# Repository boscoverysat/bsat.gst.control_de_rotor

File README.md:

# Control de Rotor

## Resumen

Este repositorio contiene la adaptación de la electrónica de control empleada para el rotor de antena basado en el proyecto **[SatNOGS](https://satnogs.org/)**

## Autoría y Licencia

- Autor: **Dailos Rafael Díaz Lara** ( ddialar@gmail.com )
- Fecha: **11/09/2015**
- Versión: **1.0.0**
- Licencia: 

## Requisitos previos

- Tener instalado el entorno de desarrollo para Arduino.
- Tener instalado el software Eagle PCB 6.5.0+.

## Procedimiento

Este repositorio contiene la adaptación de la electrónica de control empleada para el rotor de antena basado en el proyecto **[SatNOGS](https://satnogs.org/)** ([Repositorio de origen](https://github.com/satnogs/satnogs-rotator-controller)).

Esta adaptación se ha realizado para utilizar una placa **Ardino Duemilanove** en lugar de la placa *Ardiono Pro Micro*
empleada originalmente.

Para poder llevar a cabo esta adaptación, además de reorganizar la electrónica en torno a los pines del Arduino a emplear,
ha sido necesario reconfigurar los pines dentro del código fuente que será cargado en el microcontrolador.

La organización de directorios de este repositorio es la siguiente:

### [arduino](arduino/)

Contiene el archivo de código fuente que debe cargarse en el microcontrolador.

Para que este script funcione, es necesario incorporar en nuestro entorno de desarrollo, una librería adicional
que no suele venir con la instalación estándar. Dicha librería es **AccelStepper.h** y puede ser localizada
en el siguiente [enlace](https://github.com/adafruit/AccelStepper).

Para concluir, hay que indicar que la única diferencia entre el script original y el empleado en este repositorio, reside en que se ha modificado la numeración de los pines empleados para el control de los motores paso a paso, así como para la detección de la posición HOME de los ejes de Elevación y Azimuth.

En el código fuente que contiene el directorio, se ha mantenido la definición original de pines (comentada para que no tenga efecto en el código), con el propósito que sirva de referencia en futuras investigaciones.

### [img](img/)

Contiene una imagen del conexionado de la placa PCB.

### [pcb](pcb/)

Contiene el proyecto de placa de circuito impreso, realizado con el software **Eagle 6.5.0**.

### [pdf](pdf/)

Contiene el esquema electrónico y el diagrama PCB listos para ser impresos.

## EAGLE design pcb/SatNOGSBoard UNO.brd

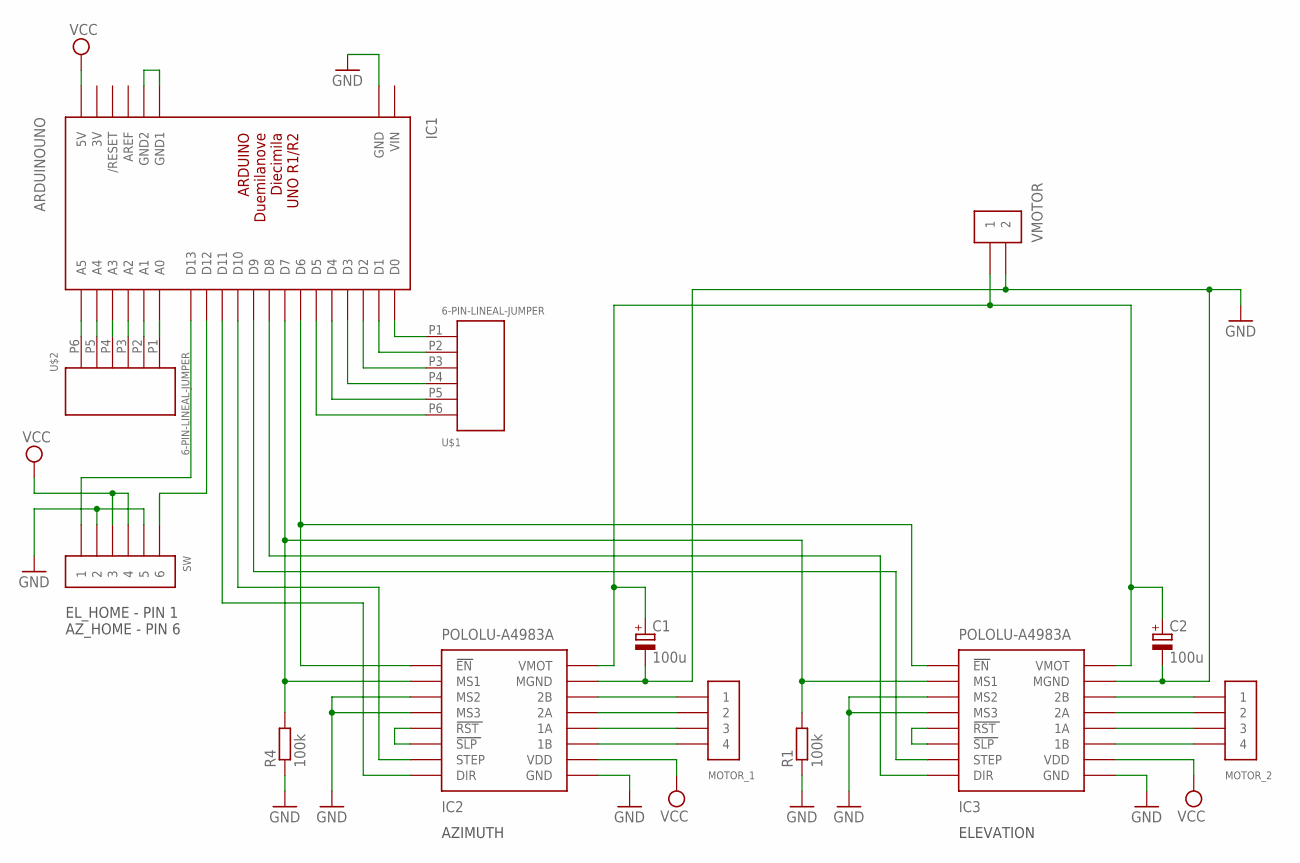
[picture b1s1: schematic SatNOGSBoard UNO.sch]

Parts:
C1, C2: 100u; B45181B
IC1: ARDUINOUNO; ARDUINO
IC2, IC3: POLOLU-A4983A; POLOLU-A4983
MOTOR_1, MOTOR_2: 4-WIRE-CONNECTOR
R1, R4: 100k; 0309/10
SW: 6-PIN-JUMPER
U$1, U$2: 6-PIN-LINEAL-JUMPER; 6-PIN-LINEAR-JUMPER
VMOTOR: 2-WIRE-CONNECTOR

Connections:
3V: IC1.3V
GND: C1.-, C2.-, IC1.GND, IC2.P$3 (MS2), IC2.P$4 (MS3), IC2.P$9 (GND), IC2.P$15 (MGND), IC3.P$3 (MS2), IC3.P$4 (MS3), IC3.P$9 (GND), IC3.P$15 (MGND), R1.1, R4.1, SW.P$2 (2), SW.P$5 (5), VMOTOR.P$2 (2)
unnamed: IC1.D6, IC2.P$1 (EN), IC3.P$1 (EN)
unnamed: IC1.D7, IC2.P$2 (MS1), IC3.P$2 (MS1), R1.2, R4.2
unnamed: IC3.P$5 (RST), IC3.P$6 (SLP)
unnamed: IC1.D9, IC3.P$7 (STEP)
unnamed: IC1.D8, IC3.P$8 (DIR)
unnamed: IC1.D0, U$1.P1
unnamed: IC1.D1, U$1.P2
unnamed: IC1.D11, IC2.P$8 (DIR)
unnamed: IC1.D12, SW.P$6 (6)
unnamed: IC3.P$14 (2B), MOTOR_2.P$1 (1)
unnamed: IC3.P$13 (2A), MOTOR_2.P$2 (2)
unnamed: IC3.P$12 (1A), MOTOR_2.P$3 (3)
unnamed: IC3.P$11 (1B), MOTOR_2.P$4 (4)
unnamed: IC2.P$5 (RST), IC2.P$6 (SLP)
unnamed: IC1.D2, U$1.P3
unnamed: IC1.D13, SW.P$1 (1)
unnamed: IC1.D3, U$1.P4
unnamed: IC1.D10, IC2.P$7 (STEP)
unnamed: IC2.P$14 (2B), MOTOR_1.P$1 (1)
unnamed: IC2.P$13 (2A), MOTOR_1.P$2 (2)
unnamed: IC2.P$12 (1A), MOTOR_1.P$3 (3)
unnamed: IC2.P$11 (1B), MOTOR_1.P$4 (4)
unnamed: IC1.D4, U$1.P5
unnamed: IC1.D5, U$1.P6
unnamed: IC1.A0, U$2.P1
unnamed: C1.+, C2.+, IC2.P$16 (VMOT), IC3.P$16 (VMOT), VMOTOR.P$1 (1)
unnamed: IC1.A1, U$2.P2
unnamed: IC1.A2, U$2.P3
unnamed: IC1.A3, U$2.P4
unnamed: IC1.A4, U$2.P5
unnamed: IC1.A5, U$2.P6
unnamed: IC1.GND1, IC1.GND2
VCC: IC1.5V, IC2.P$10 (VDD), IC3.P$10 (VDD), SW.P$3 (3), SW.P$4 (4)
VIN: IC1.VIN

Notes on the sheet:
ELEVATION
AZIMUTH
EL_HOME - PIN 1 AZ_HOME - PIN 6

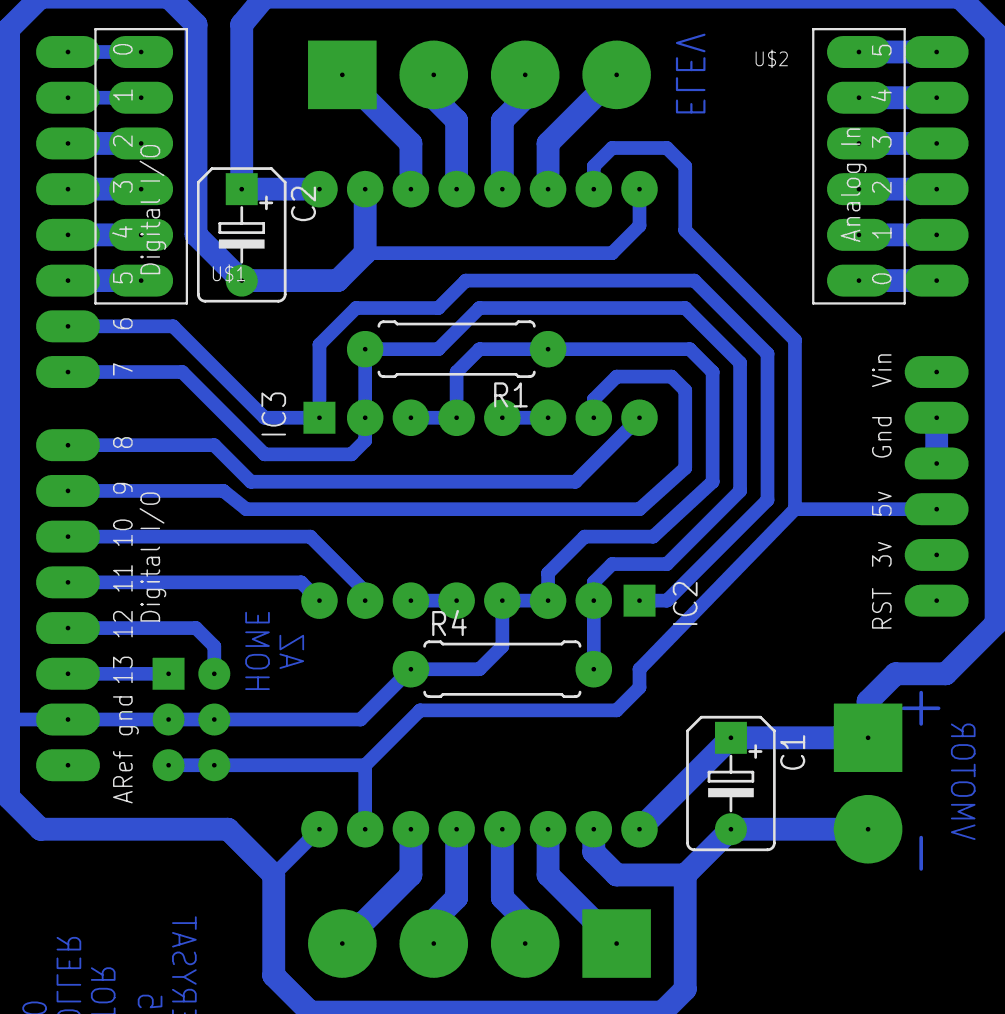
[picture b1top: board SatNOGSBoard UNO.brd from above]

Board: 2 copper layers, 13 parts (0 on the bottom side), 34 nets.

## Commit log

2015-09-10 Repositorio creado
2015-09-12 Añadido diseño de PCB y script de control para Arduino Duemilanove.
2015-09-15 Añadido sketch para la comprobación del funcionamiento de los pololus

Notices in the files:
README.md:
Autoría y Licencia:
- Licencia: [Creaive Commons 4.0 logo](http://creativecommons.org/licenses/by-nc-sa/4.0/)
